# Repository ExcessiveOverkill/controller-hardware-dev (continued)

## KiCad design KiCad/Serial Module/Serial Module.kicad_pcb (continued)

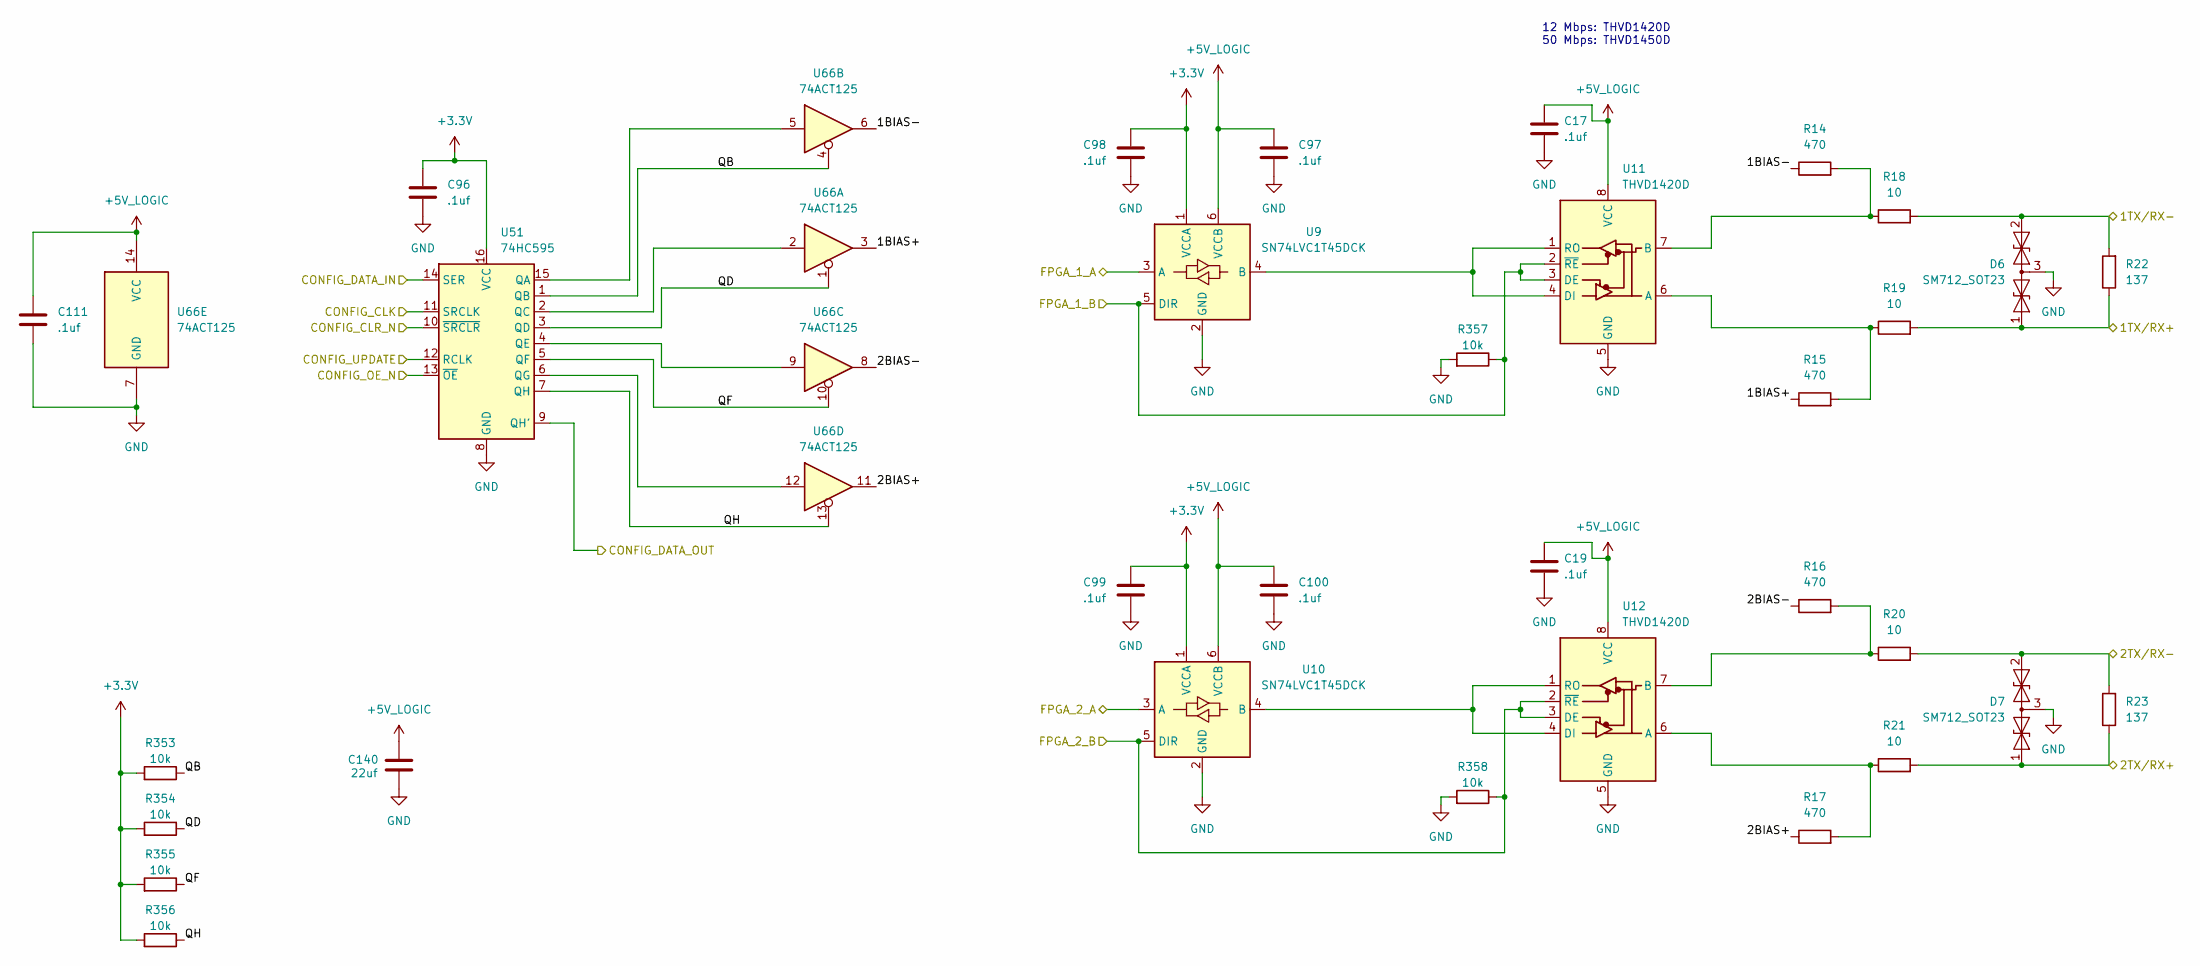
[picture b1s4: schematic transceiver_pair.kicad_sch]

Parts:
C17, C19, C96, C97, C98, C99, C100, C111: .1uf; C_0402_1005Metric; Part number CC0402KRX7R9BB104; LCSC# C131394
C140: 22uf; C_0805_2012Metric; Part number CC0805MKX5R8BB226; LCSC# C784585
D6, D7: SM712_SOT23; SOT-23; Part number SM712; LCSC# C502564
R14, R15, R16, R17: 470; R_0805_2012Metric; Part number 0603WAF4700T5E; LCSC# C23179
R18, R19, R20, R21: 10; R_0603_1608Metric; Part number 0603WAF100JT5E; LCSC# C22859
R22, R23: 137; R_0603_1608Metric; Part number 0603WAF1370T5E; LCSC# C22873
R353, R354, R355, R356, R357, R358: 10k; R_0402_1005Metric; Part number RC0402FR-0710KL; LCSC# C60490
U9, U10: SN74LVC1T45DCK; SOT-363_SC-70-6; Part number SN74LVC1T45DCKR; LCSC# C9382
U11, U12: THVD1420D; SOIC-8_3.9x4.9mm_P1.27mm; Part number THVD1420DR; LCSC# C3235215
U51: 74HC595; DHVQFN-16-1EP_2.5x3.5mm_P0.5mm_EP1x2mm; Part number 74HC595BQ,115; LCSC# C730243
U66: 74ACT125; TSSOP-14_4.4x5mm_P0.65mm; Part number SN74ACT125PWR; LCSC# C52940839

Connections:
+3.3V: C96.1, C98.1, C99.1, R353.2, R354.2, R355.2, R356.2, U9.1 (VCCA), U10.1 (VCCA), U51.16 (VCC); also elsewhere on the board
+5V_LOGIC: C17.1, C19.1, C97.1, C100.1, C111.1, C140.2, U9.6 (VCCB), U10.6 (VCCB), U11.8 (VCC), U12.8 (VCC), U66.14 (VCC); also elsewhere on the board
/MCU/CONFIG_CLK: U51.11 (SRCLK); also elsewhere on the board
/MCU/CONFIG_CLR_N: U51.10 (~SRCLR); also elsewhere on the board
/MCU/CONFIG_DATA: U51.14 (SER); also elsewhere on the board
/MCU/CONFIG_OE_N: U51.13 (~OE); also elsewhere on the board
/MCU/CONFIG_UPDATE: U51.12 (RCLK); also elsewhere on the board
/Transceivers/FPGA MUX/FPGA_PORT_1_PIN_0: U9.3 (A); also elsewhere on the board
/Transceivers/FPGA MUX/FPGA_PORT_1_PIN_1: R357.1, U9.5 (DIR), U11.2 (~RE), U11.3 (DE); also elsewhere on the board
/Transceivers/FPGA MUX/FPGA_PORT_1_PIN_2: U10.3 (A); also elsewhere on the board
/Transceivers/FPGA MUX/FPGA_PORT_1_PIN_3: R358.1, U10.5 (DIR), U12.2 (~RE), U12.3 (DE); also elsewhere on the board
/Transceivers/PORT_1_DATA_1+: D6.1 (A1), R19.2, R22.1; also elsewhere on the board
/Transceivers/PORT_1_DATA_1-: D6.2 (A2), R18.2, R22.2; also elsewhere on the board
/Transceivers/PORT_1_DATA_2+: D7.1 (A1), R21.2, R23.1; also elsewhere on the board
/Transceivers/PORT_1_DATA_2-: D7.2 (A2), R20.2, R23.2; also elsewhere on the board
/Transceivers/Transceiver pair/1BIAS+: R15.1, U66.3
/Transceivers/Transceiver pair/1BIAS-: R14.1, U66.6
/Transceivers/Transceiver pair/2BIAS+: R17.1, U66.11
/Transceivers/Transceiver pair/2BIAS-: R16.1, U66.8
/Transceivers/Transceiver pair/CONFIG_DATA_OUT: U51.9 (QH'); also elsewhere on the board
/Transceivers/Transceiver pair/QB: R353.1, U51.1 (QB), U66.4
/Transceivers/Transceiver pair/QD: R354.1, U51.3 (QD), U66.1
/Transceivers/Transceiver pair/QF: R355.1, U51.5 (QF), U66.10
/Transceivers/Transceiver pair/QH: R356.1, U51.7 (QH), U66.13
GND: C17.2, C19.2, C96.2, C97.2, C98.2, C99.2, C100.2, C111.2, C140.1, D6.3 (common), D7.3 (common), R357.2, R358.2, U9.2 (GND), U10.2 (GND), U11.5 (GND), U12.5 (GND), U51.8 (GND), U66.7 (GND); also elsewhere on the board
unnamed: U10.4 (B), U12.1 (RO), U12.4 (DI)
unnamed: R15.2, R19.1, U11.6 (A)
unnamed: R14.2, R18.1, U11.7 (B)
unnamed: U9.4 (B), U11.1 (RO), U11.4 (DI)
unnamed: R17.2, R21.1, U12.6 (A)
unnamed: R16.2, R20.1, U12.7 (B)
unnamed: U51.15 (QA), U66.5
unnamed: U51.2 (QC), U66.2
unnamed: U51.4 (QE), U66.9
unnamed: U51.6 (QG), U66.12

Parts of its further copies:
C25, C26, C31, C32, C79, C80, C81, C82, C83, C84, C85, C86, C87, C88, C103, C104, C105, C106, C107, C108, C109, C117, C118, C119, C120, C121, C122, C123, C124, C125, C126, C127, C128, C129, C130, C131, C145, C146, C147, C160, C161, C162, C163, C164, C165, C167, C168, C169, C170, C171, C172, C174, C175, C176, C177, C178: .1uf; C_0402_1005Metric; Part number CC0402KRX7R9BB104; LCSC# C131394
C141, C142, C143, C144, C159, C166, C173: 22uf; C_0805_2012Metric; Part number CC0805MKX5R8BB226; LCSC# C784585
D36, D37, D38, D39, D40, D41, D42, D43, D44, D45, D46, D47, D48, D49: SM712_SOT23; SOT-23; Part number SM712; LCSC# C502564
R64, R65, R66, R67, R74, R75, R76, R77, R84, R85, R86, R87, R94, R95, R96, R97, R104, R105, R106, R107, R114, R115, R116, R117, R124, R125, R126, R127: 470; R_0805_2012Metric; Part number 0603WAF4700T5E; LCSC# C23179
R68, R69, R70, R71, R78, R79, R80, R81, R88, R89, R90, R91, R98, R99, R100, R101, R108, R109, R110, R111, R118, R119, R120, R121, R128, R129, R130, R131: 10; R_0603_1608Metric; Part number 0603WAF100JT5E; LCSC# C22859
R72, R73, R82, R83, R92, R93, R102, R103, R112, R113, R122, R123, R132, R133: 137; R_0603_1608Metric; Part number 0603WAF1370T5E; LCSC# C22873
R359, R360, R361, R362, R363, R364, R365, R366, R367, R368, R369, R370, R371, R372, R373, R374, R375, R376, R377, R378, R379, R380, R381, R382, R383, R384, R405, R406, R407, R408, R409, R410, R411, R412, R413, R414, R415, R416, R417, R418, R419, R420: 10k; R_0402_1005Metric; Part number RC0402FR-0710KL; LCSC# C60490
U16, U17, U28, U29, U32, U33, U36, U37, U40, U41, U44, U45, U48, U49: SN74LVC1T45DCK; SOT-363_SC-70-6; Part number SN74LVC1T45DCKR; LCSC# C9382
U26, U27, U30, U31, U34, U35, U38, U39, U42, U43, U46, U47, U50, U61: THVD1420D; SOIC-8_3.9x4.9mm_P1.27mm; Part number THVD1420DR; LCSC# C3235215
U54, U55, U56, U57, U58, U59, U60: 74HC595; DHVQFN-16-1EP_2.5x3.5mm_P0.5mm_EP1x2mm; Part number 74HC595BQ,115; LCSC# C730243
U67, U68, U69, U70, U71, U72, U73: 74ACT125; TSSOP-14_4.4x5mm_P0.65mm; Part number SN74ACT125PWR; LCSC# C52940839

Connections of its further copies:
+3.3V: C103.1, C104.1, C105.1, C108.1, C109.1, C119.1, C123.1, C124.1, C125.1, C129.1, C130.1, C131.1, C160.1, C161.1, C162.1, C167.1, C168.1, C169.1, C174.1, C175.1, C176.1, R359.2, R360.2, R361.2, R362.2, R365.2, R366.2, R367.2, R368.2, R371.2, R372.2, R373.2, R374.2, R377.2, R378.2, R379.2, R380.2, R383.2, R384.2, R405.2, R406.2, R409.2, R410.2, R411.2, R412.2, R415.2, R416.2, R417.2, R418.2, U16.1 (VCCA), U17.1 (VCCA), U28.1 (VCCA), U29.1 (VCCA), U32.1 (VCCA), U33.1 (VCCA), U36.1 (VCCA), U37.1 (VCCA), U40.1 (VCCA), U41.1 (VCCA), U44.1 (VCCA), U45.1 (VCCA), U48.1 (VCCA), U49.1 (VCCA), U54.16 (VCC), U55.16 (VCC), U56.16 (VCC), U57.16 (VCC), U58.16 (VCC), U59.16 (VCC), U60.16 (VCC); also elsewhere on the board
+5V_LOGIC: C25.1, C26.1, C31.1, C32.1, C79.1, C80.1, C81.1, C82.1, C83.1, C84.1, C85.1, C86.1, C87.1, C88.1, C106.1, C107.1, C117.1, C118.1, C120.1, C121.1, C122.1, C126.1, C127.1, C128.1, C141.2, C142.2, C143.2, C144.2, C145.1, C146.1, C147.1, C159.2, C163.1, C164.1, C165.1, C166.2, C170.1, C171.1, C172.1, C173.2, C177.1, C178.1, U16.6 (VCCB), U17.6 (VCCB), U26.8 (VCC), U27.8 (VCC), U28.6 (VCCB), U29.6 (VCCB), U30.8 (VCC), U31.8 (VCC), U32.6 (VCCB), U33.6 (VCCB), U34.8 (VCC), U35.8 (VCC), U36.6 (VCCB), U37.6 (VCCB), U38.8 (VCC), U39.8 (VCC), U40.6 (VCCB), U41.6 (VCCB), U42.8 (VCC), U43.8 (VCC), U44.6 (VCCB), U45.6 (VCCB), U46.8 (VCC), U47.8 (VCC), U48.6 (VCCB), U49.6 (VCCB), U50.8 (VCC), U61.8 (VCC), U67.14 (VCC), U68.14 (VCC), U69.14 (VCC), U70.14 (VCC), U71.14 (VCC), U72.14 (VCC), U73.14 (VCC); also elsewhere on the board
/MCU/CONFIG_CLK: U54.11 (SRCLK), U55.11 (SRCLK), U56.11 (SRCLK), U57.11 (SRCLK), U58.11 (SRCLK), U59.11 (SRCLK), U60.11 (SRCLK); also elsewhere on the board
/MCU/CONFIG_CLR_N: U54.10 (~SRCLR), U55.10 (~SRCLR), U56.10 (~SRCLR), U57.10 (~SRCLR), U58.10 (~SRCLR), U59.10 (~SRCLR), U60.10 (~SRCLR); also elsewhere on the board
/MCU/CONFIG_OE_N: U54.13 (~OE), U55.13 (~OE), U56.13 (~OE), U57.13 (~OE), U58.13 (~OE), U59.13 (~OE), U60.13 (~OE); also elsewhere on the board
/MCU/CONFIG_UPDATE: U54.12 (RCLK), U55.12 (RCLK), U56.12 (RCLK), U57.12 (RCLK), U58.12 (RCLK), U59.12 (RCLK), U60.12 (RCLK); also elsewhere on the board
/Transceivers/FPGA MUX/FPGA_PORT_2_PIN_0: U16.3 (A); also elsewhere on the board
/Transceivers/FPGA MUX/FPGA_PORT_2_PIN_1: R363.1, U16.5 (DIR), U26.2 (~RE), U26.3 (DE); also elsewhere on the board
/Transceivers/FPGA MUX/FPGA_PORT_2_PIN_2: U17.3 (A); also elsewhere on the board
/Transceivers/FPGA MUX/FPGA_PORT_2_PIN_3: R364.1, U17.5 (DIR), U27.2 (~RE), U27.3 (DE); also elsewhere on the board
/Transceivers/FPGA MUX/FPGA_PORT_3_PIN_0: U28.3 (A); also elsewhere on the board
/Transceivers/FPGA MUX/FPGA_PORT_3_PIN_1: R369.1, U28.5 (DIR), U30.2 (~RE), U30.3 (DE); also elsewhere on the board
/Transceivers/FPGA MUX/FPGA_PORT_3_PIN_2: U29.3 (A); also elsewhere on the board
/Transceivers/FPGA MUX/FPGA_PORT_3_PIN_3: R370.1, U29.5 (DIR), U31.2 (~RE), U31.3 (DE); also elsewhere on the board
/Transceivers/FPGA MUX/FPGA_PORT_4_PIN_0: U32.3 (A); also elsewhere on the board
/Transceivers/FPGA MUX/FPGA_PORT_4_PIN_1: R375.1, U32.5 (DIR), U34.2 (~RE), U34.3 (DE); also elsewhere on the board
/Transceivers/FPGA MUX/FPGA_PORT_4_PIN_2: U33.3 (A); also elsewhere on the board
/Transceivers/FPGA MUX/FPGA_PORT_4_PIN_3: R376.1, U33.5 (DIR), U35.2 (~RE), U35.3 (DE); also elsewhere on the board
/Transceivers/FPGA MUX/FPGA_PORT_5_PIN_0: U36.3 (A); also elsewhere on the board
/Transceivers/FPGA MUX/FPGA_PORT_5_PIN_1: R381.1, U36.5 (DIR), U38.2 (~RE), U38.3 (DE); also elsewhere on the board
/Transceivers/FPGA MUX/FPGA_PORT_5_PIN_2: U37.3 (A); also elsewhere on the board
/Transceivers/FPGA MUX/FPGA_PORT_5_PIN_3: R382.1, U37.5 (DIR), U39.2 (~RE), U39.3 (DE); also elsewhere on the board
/Transceivers/FPGA MUX/FPGA_PORT_6_PIN_0: U40.3 (A); also elsewhere on the board
/Transceivers/FPGA MUX/FPGA_PORT_6_PIN_1: R407.1, U40.5 (DIR), U42.2 (~RE), U42.3 (DE); also elsewhere on the board
/Transceivers/FPGA MUX/FPGA_PORT_6_PIN_2: U41.3 (A); also elsewhere on the board
/Transceivers/FPGA MUX/FPGA_PORT_6_PIN_3: R408.1, U41.5 (DIR), U43.2 (~RE), U43.3 (DE); also elsewhere on the board
/Transceivers/FPGA MUX/FPGA_PORT_7_PIN_0: U44.3 (A); also elsewhere on the board
/Transceivers/FPGA MUX/FPGA_PORT_7_PIN_1: R413.1, U44.5 (DIR), U46.2 (~RE), U46.3 (DE); also elsewhere on the board
/Transceivers/FPGA MUX/FPGA_PORT_7_PIN_2: U45.3 (A); also elsewhere on the board
/Transceivers/FPGA MUX/FPGA_PORT_7_PIN_3: R414.1, U45.5 (DIR), U47.2 (~RE), U47.3 (DE); also elsewhere on the board
/Transceivers/FPGA MUX/FPGA_PORT_8_PIN_0: U48.3 (A); also elsewhere on the board
/Transceivers/FPGA MUX/FPGA_PORT_8_PIN_1: R419.1, U48.5 (DIR), U50.2 (~RE), U50.3 (DE); also elsewhere on the board
/Transceivers/FPGA MUX/FPGA_PORT_8_PIN_2: U49.3 (A); also elsewhere on the board
/Transceivers/FPGA MUX/FPGA_PORT_8_PIN_3: R420.1, U49.5 (DIR), U61.2 (~RE), U61.3 (DE); also elsewhere on the board
/Transceivers/PORT_2_DATA_1+: D36.1 (A1), R69.2, R72.1; also elsewhere on the board
/Transceivers/PORT_2_DATA_1-: D36.2 (A2), R68.2, R72.2; also elsewhere on the board
/Transceivers/PORT_2_DATA_2+: D37.1 (A1), R71.2, R73.1; also elsewhere on the board
/Transceivers/PORT_2_DATA_2-: D37.2 (A2), R70.2, R73.2; also elsewhere on the board
/Transceivers/PORT_3_DATA_1+: D38.1 (A1), R79.2, R82.1; also elsewhere on the board
/Transceivers/PORT_3_DATA_1-: D38.2 (A2), R78.2, R82.2; also elsewhere on the board
/Transceivers/PORT_3_DATA_2+: D39.1 (A1), R81.2, R83.1; also elsewhere on the board
/Transceivers/PORT_3_DATA_2-: D39.2 (A2), R80.2, R83.2; also elsewhere on the board
/Transceivers/PORT_4_DATA_1+: D40.1 (A1), R89.2, R92.1; also elsewhere on the board
/Transceivers/PORT_4_DATA_1-: D40.2 (A2), R88.2, R92.2; also elsewhere on the board
/Transceivers/PORT_4_DATA_2+: D41.1 (A1), R91.2, R93.1; also elsewhere on the board
/Transceivers/PORT_4_DATA_2-: D41.2 (A2), R90.2, R93.2; also elsewhere on the board
/Transceivers/PORT_5_DATA_1+: D42.1 (A1), R99.2, R102.1; also elsewhere on the board
/Transceivers/PORT_5_DATA_1-: D42.2 (A2), R98.2, R102.2; also elsewhere on the board
/Transceivers/PORT_5_DATA_2+: D43.1 (A1), R101.2, R103.1; also elsewhere on the board
/Transceivers/PORT_5_DATA_2-: D43.2 (A2), R100.2, R103.2; also elsewhere on the board
/Transceivers/PORT_6_DATA_1+: D44.1 (A1), R109.2, R112.1; also elsewhere on the board
/Transceivers/PORT_6_DATA_1-: D44.2 (A2), R108.2, R112.2; also elsewhere on the board
/Transceivers/PORT_6_DATA_2+: D45.1 (A1), R111.2, R113.1; also elsewhere on the board
/Transceivers/PORT_6_DATA_2-: D45.2 (A2), R110.2, R113.2; also elsewhere on the board
/Transceivers/PORT_7_DATA_1+: D46.1 (A1), R119.2, R122.1; also elsewhere on the board
/Transceivers/PORT_7_DATA_1-: D46.2 (A2), R118.2, R122.2; also elsewhere on the board
/Transceivers/PORT_7_DATA_2+: D47.1 (A1), R121.2, R123.1; also elsewhere on the board
/Transceivers/PORT_7_DATA_2-: D47.2 (A2), R120.2, R123.2; also elsewhere on the board
/Transceivers/PORT_8_DATA_1+: D48.1 (A1), R129.2, R132.1; also elsewhere on the board
/Transceivers/PORT_8_DATA_1-: D48.2 (A2), R128.2, R132.2; also elsewhere on the board
/Transceivers/PORT_8_DATA_2+: D49.1 (A1), R131.2, R133.1; also elsewhere on the board
/Transceivers/PORT_8_DATA_2-: D49.2 (A2), R130.2, R133.2; also elsewhere on the board
/Transceivers/Port Power/CONFIG_DATA_IN: U60.9 (QH'); also elsewhere on the board
/Transceivers/Transceiver pair1/1BIAS+: R65.1, U67.3
/Transceivers/Transceiver pair1/1BIAS-: R64.1, U67.6
/Transceivers/Transceiver pair1/2BIAS+: R67.1, U67.11
/Transceivers/Transceiver pair1/2BIAS-: R66.1, U67.8
/Transceivers/Transceiver pair1/CONFIG_DATA_OUT: U54.9 (QH'), U55.14 (SER)
/Transceivers/Transceiver pair1/QB: R359.1, U54.1 (QB), U67.4
/Transceivers/Transceiver pair1/QD: R360.1, U54.3 (QD), U67.1
/Transceivers/Transceiver pair1/QF: R361.1, U54.5 (QF), U67.10
/Transceivers/Transceiver pair1/QH: R362.1, U54.7 (QH), U67.13
/Transceivers/Transceiver pair2/1BIAS+: R75.1, U68.3
/Transceivers/Transceiver pair2/1BIAS-: R74.1, U68.6
/Transceivers/Transceiver pair2/2BIAS+: R77.1, U68.11
/Transceivers/Transceiver pair2/2BIAS-: R76.1, U68.8
/Transceivers/Transceiver pair2/CONFIG_DATA_OUT: U55.9 (QH'), U56.14 (SER)
/Transceivers/Transceiver pair2/QB: R365.1, U55.1 (QB), U68.4
/Transceivers/Transceiver pair2/QD: R366.1, U55.3 (QD), U68.1
/Transceivers/Transceiver pair2/QF: R367.1, U55.5 (QF), U68.10
/Transceivers/Transceiver pair2/QH: R368.1, U55.7 (QH), U68.13
/Transceivers/Transceiver pair3/1BIAS+: R85.1, U69.3
/Transceivers/Transceiver pair3/1BIAS-: R84.1, U69.6
/Transceivers/Transceiver pair3/2BIAS+: R87.1, U69.11
/Transceivers/Transceiver pair3/2BIAS-: R86.1, U69.8
/Transceivers/Transceiver pair3/CONFIG_DATA_OUT: U56.9 (QH'), U57.14 (SER)
/Transceivers/Transceiver pair3/QB: R371.1, U56.1 (QB), U69.4
/Transceivers/Transceiver pair3/QD: R372.1, U56.3 (QD), U69.1
/Transceivers/Transceiver pair3/QF: R373.1, U56.5 (QF), U69.10
/Transceivers/Transceiver pair3/QH: R374.1, U56.7 (QH), U69.13
/Transceivers/Transceiver pair4/1BIAS+: R95.1, U70.3
/Transceivers/Transceiver pair4/1BIAS-: R94.1, U70.6
/Transceivers/Transceiver pair4/2BIAS+: R97.1, U70.11
/Transceivers/Transceiver pair4/2BIAS-: R96.1, U70.8
/Transceivers/Transceiver pair4/CONFIG_DATA_OUT: U57.9 (QH'), U58.14 (SER)
/Transceivers/Transceiver pair4/QB: R377.1, U57.1 (QB), U70.4
/Transceivers/Transceiver pair4/QD: R378.1, U57.3 (QD), U70.1
/Transceivers/Transceiver pair4/QF: R379.1, U57.5 (QF), U70.10
/Transceivers/Transceiver pair4/QH: R380.1, U57.7 (QH), U70.13
/Transceivers/Transceiver pair5/1BIAS+: R105.1, U71.3
/Transceivers/Transceiver pair5/1BIAS-: R104.1, U71.6
/Transceivers/Transceiver pair5/2BIAS+: R107.1, U71.11
/Transceivers/Transceiver pair5/2BIAS-: R106.1, U71.8
/Transceivers/Transceiver pair5/CONFIG_DATA_OUT: U58.9 (QH'), U59.14 (SER)
/Transceivers/Transceiver pair5/QB: R383.1, U58.1 (QB), U71.4
/Transceivers/Transceiver pair5/QD: R384.1, U58.3 (QD), U71.1
/Transceivers/Transceiver pair5/QF: R405.1, U58.5 (QF), U71.10
/Transceivers/Transceiver pair5/QH: R406.1, U58.7 (QH), U71.13
/Transceivers/Transceiver pair6/1BIAS+: R115.1, U72.3
/Transceivers/Transceiver pair6/1BIAS-: R114.1, U72.6
/Transceivers/Transceiver pair6/2BIAS+: R117.1, U72.11
/Transceivers/Transceiver pair6/2BIAS-: R116.1, U72.8
/Transceivers/Transceiver pair6/CONFIG_DATA_OUT: U59.9 (QH'), U60.14 (SER)
/Transceivers/Transceiver pair6/QB: R409.1, U59.1 (QB), U72.4
/Transceivers/Transceiver pair6/QD: R410.1, U59.3 (QD), U72.1
/Transceivers/Transceiver pair6/QF: R411.1, U59.5 (QF), U72.10
/Transceivers/Transceiver pair6/QH: R412.1, U59.7 (QH), U72.13
/Transceivers/Transceiver pair7/1BIAS+: R125.1, U73.3
/Transceivers/Transceiver pair7/1BIAS-: R124.1, U73.6
/Transceivers/Transceiver pair7/2BIAS+: R127.1, U73.11
/Transceivers/Transceiver pair7/2BIAS-: R126.1, U73.8
/Transceivers/Transceiver pair7/QB: R415.1, U60.1 (QB), U73.4
/Transceivers/Transceiver pair7/QD: R416.1, U60.3 (QD), U73.1
/Transceivers/Transceiver pair7/QF: R417.1, U60.5 (QF), U73.10
/Transceivers/Transceiver pair7/QH: R418.1, U60.7 (QH), U73.13
/Transceivers/Transceiver pair/CONFIG_DATA_OUT: U54.14 (SER); also elsewhere on the board
GND: C25.2, C26.2, C31.2, C32.2, C79.2, C80.2, C81.2, C82.2, C83.2, C84.2, C85.2, C86.2, C87.2, C88.2, C103.2, C104.2, C105.2, C106.2, C107.2, C108.2, C109.2, C117.2, C118.2, C119.2, C120.2, C121.2, C122.2, C123.2, C124.2, C125.2, C126.2, C127.2, C128.2, C129.2, C130.2, C131.2, C141.1, C142.1, C143.1, C144.1, C145.2, C146.2, C147.2, C159.1, C160.2, C161.2, C162.2, C163.2, C164.2, C165.2, C166.1, C167.2, C168.2, C169.2, C170.2, C171.2, C172.2, C173.1, C174.2, C175.2, C176.2, C177.2, C178.2, D36.3 (common), D37.3 (common), D38.3 (common), D39.3 (common), D40.3 (common), D41.3 (common), D42.3 (common), D43.3 (common), D44.3 (common), D45.3 (common), D46.3 (common), D47.3 (common), D48.3 (common), D49.3 (common), R363.2, R364.2, R369.2, R370.2, R375.2, R376.2, R381.2, R382.2, R407.2, R408.2, R413.2, R414.2, R419.2, R420.2, U16.2 (GND), U17.2 (GND), U26.5 (GND), U27.5 (GND), U28.2 (GND), U29.2 (GND), U30.5 (GND), U31.5 (GND), U32.2 (GND), U33.2 (GND), U34.5 (GND), U35.5 (GND), U36.2 (GND), U37.2 (GND), U38.5 (GND), U39.5 (GND), U40.2 (GND), U41.2 (GND), U42.5 (GND), U43.5 (GND), U44.2 (GND), U45.2 (GND), U46.5 (GND), U47.5 (GND), U48.2 (GND), U49.2 (GND), U50.5 (GND), U54.8 (GND), U55.8 (GND), U56.8 (GND), U57.8 (GND), U58.8 (GND), U59.8 (GND), U60.8 (GND), U61.5 (GND), U67.7 (GND), U68.7 (GND), U69.7 (GND), U70.7 (GND), U71.7 (GND), U72.7 (GND), U73.7 (GND); also elsewhere on the board
unnamed: U16.4 (B), U26.1 (RO), U26.4 (DI)
unnamed: U17.4 (B), U27.1 (RO), U27.4 (DI)
unnamed: R65.2, R69.1, U26.6 (A)
unnamed: R64.2, R68.1, U26.7 (B)
unnamed: R67.2, R71.1, U27.6 (A)
unnamed: R66.2, R70.1, U27.7 (B)
unnamed: U28.4 (B), U30.1 (RO), U30.4 (DI)
unnamed: U29.4 (B), U31.1 (RO), U31.4 (DI)
unnamed: R75.2, R79.1, U30.6 (A)
unnamed: R74.2, R78.1, U30.7 (B)
unnamed: R77.2, R81.1, U31.6 (A)
unnamed: R76.2, R80.1, U31.7 (B)
unnamed: U32.4 (B), U34.1 (RO), U34.4 (DI)
unnamed: U33.4 (B), U35.1 (RO), U35.4 (DI)
unnamed: R85.2, R89.1, U34.6 (A)
unnamed: R84.2, R88.1, U34.7 (B)
unnamed: R87.2, R91.1, U35.6 (A)
unnamed: R86.2, R90.1, U35.7 (B)
unnamed: U36.4 (B), U38.1 (RO), U38.4 (DI)
unnamed: U37.4 (B), U39.1 (RO), U39.4 (DI)
unnamed: R95.2, R99.1, U38.6 (A)
unnamed: R94.2, R98.1, U38.7 (B)
unnamed: R97.2, R101.1, U39.6 (A)
unnamed: R96.2, R100.1, U39.7 (B)
unnamed: U40.4 (B), U42.1 (RO), U42.4 (DI)
unnamed: U41.4 (B), U43.1 (RO), U43.4 (DI)
unnamed: R105.2, R109.1, U42.6 (A)
unnamed: R104.2, R108.1, U42.7 (B)
unnamed: R107.2, R111.1, U43.6 (A)
unnamed: R106.2, R110.1, U43.7 (B)
unnamed: U44.4 (B), U46.1 (RO), U46.4 (DI)
unnamed: U45.4 (B), U47.1 (RO), U47.4 (DI)
unnamed: R115.2, R119.1, U46.6 (A)
unnamed: R114.2, R118.1, U46.7 (B)
unnamed: R117.2, R121.1, U47.6 (A)
unnamed: R116.2, R120.1, U47.7 (B)
unnamed: U48.4 (B), U50.1 (RO), U50.4 (DI)
unnamed: U49.4 (B), U61.1 (RO), U61.4 (DI)
unnamed: R125.2, R129.1, U50.6 (A)
unnamed: R124.2, R128.1, U50.7 (B)
unnamed: U54.15 (QA), U67.5
unnamed: U54.2 (QC), U67.2
unnamed: U54.4 (QE), U67.9
unnamed: U54.6 (QG), U67.12
unnamed: U55.15 (QA), U68.5
unnamed: U55.2 (QC), U68.2
unnamed: U55.4 (QE), U68.9
unnamed: U55.6 (QG), U68.12
unnamed: U56.15 (QA), U69.5
unnamed: U56.2 (QC), U69.2
unnamed: U56.4 (QE), U69.9
unnamed: U56.6 (QG), U69.12
unnamed: U57.15 (QA), U70.5
unnamed: U57.2 (QC), U70.2
unnamed: U57.4 (QE), U70.9
unnamed: U57.6 (QG), U70.12
unnamed: U58.15 (QA), U71.5
unnamed: U58.2 (QC), U71.2
unnamed: U58.4 (QE), U71.9
unnamed: U58.6 (QG), U71.12
unnamed: U59.15 (QA), U72.5
unnamed: U59.2 (QC), U72.2
unnamed: U59.4 (QE), U72.9
unnamed: U59.6 (QG), U72.12
unnamed: U60.15 (QA), U73.5
unnamed: U60.2 (QC), U73.2
unnamed: U60.4 (QE), U73.9
unnamed: U60.6 (QG), U73.12
unnamed: R127.2, R131.1, U61.6 (A)
unnamed: R126.2, R130.1, U61.7 (B)

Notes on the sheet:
12 Mbps: THVD1420D 50 Mbps: THVD1450D

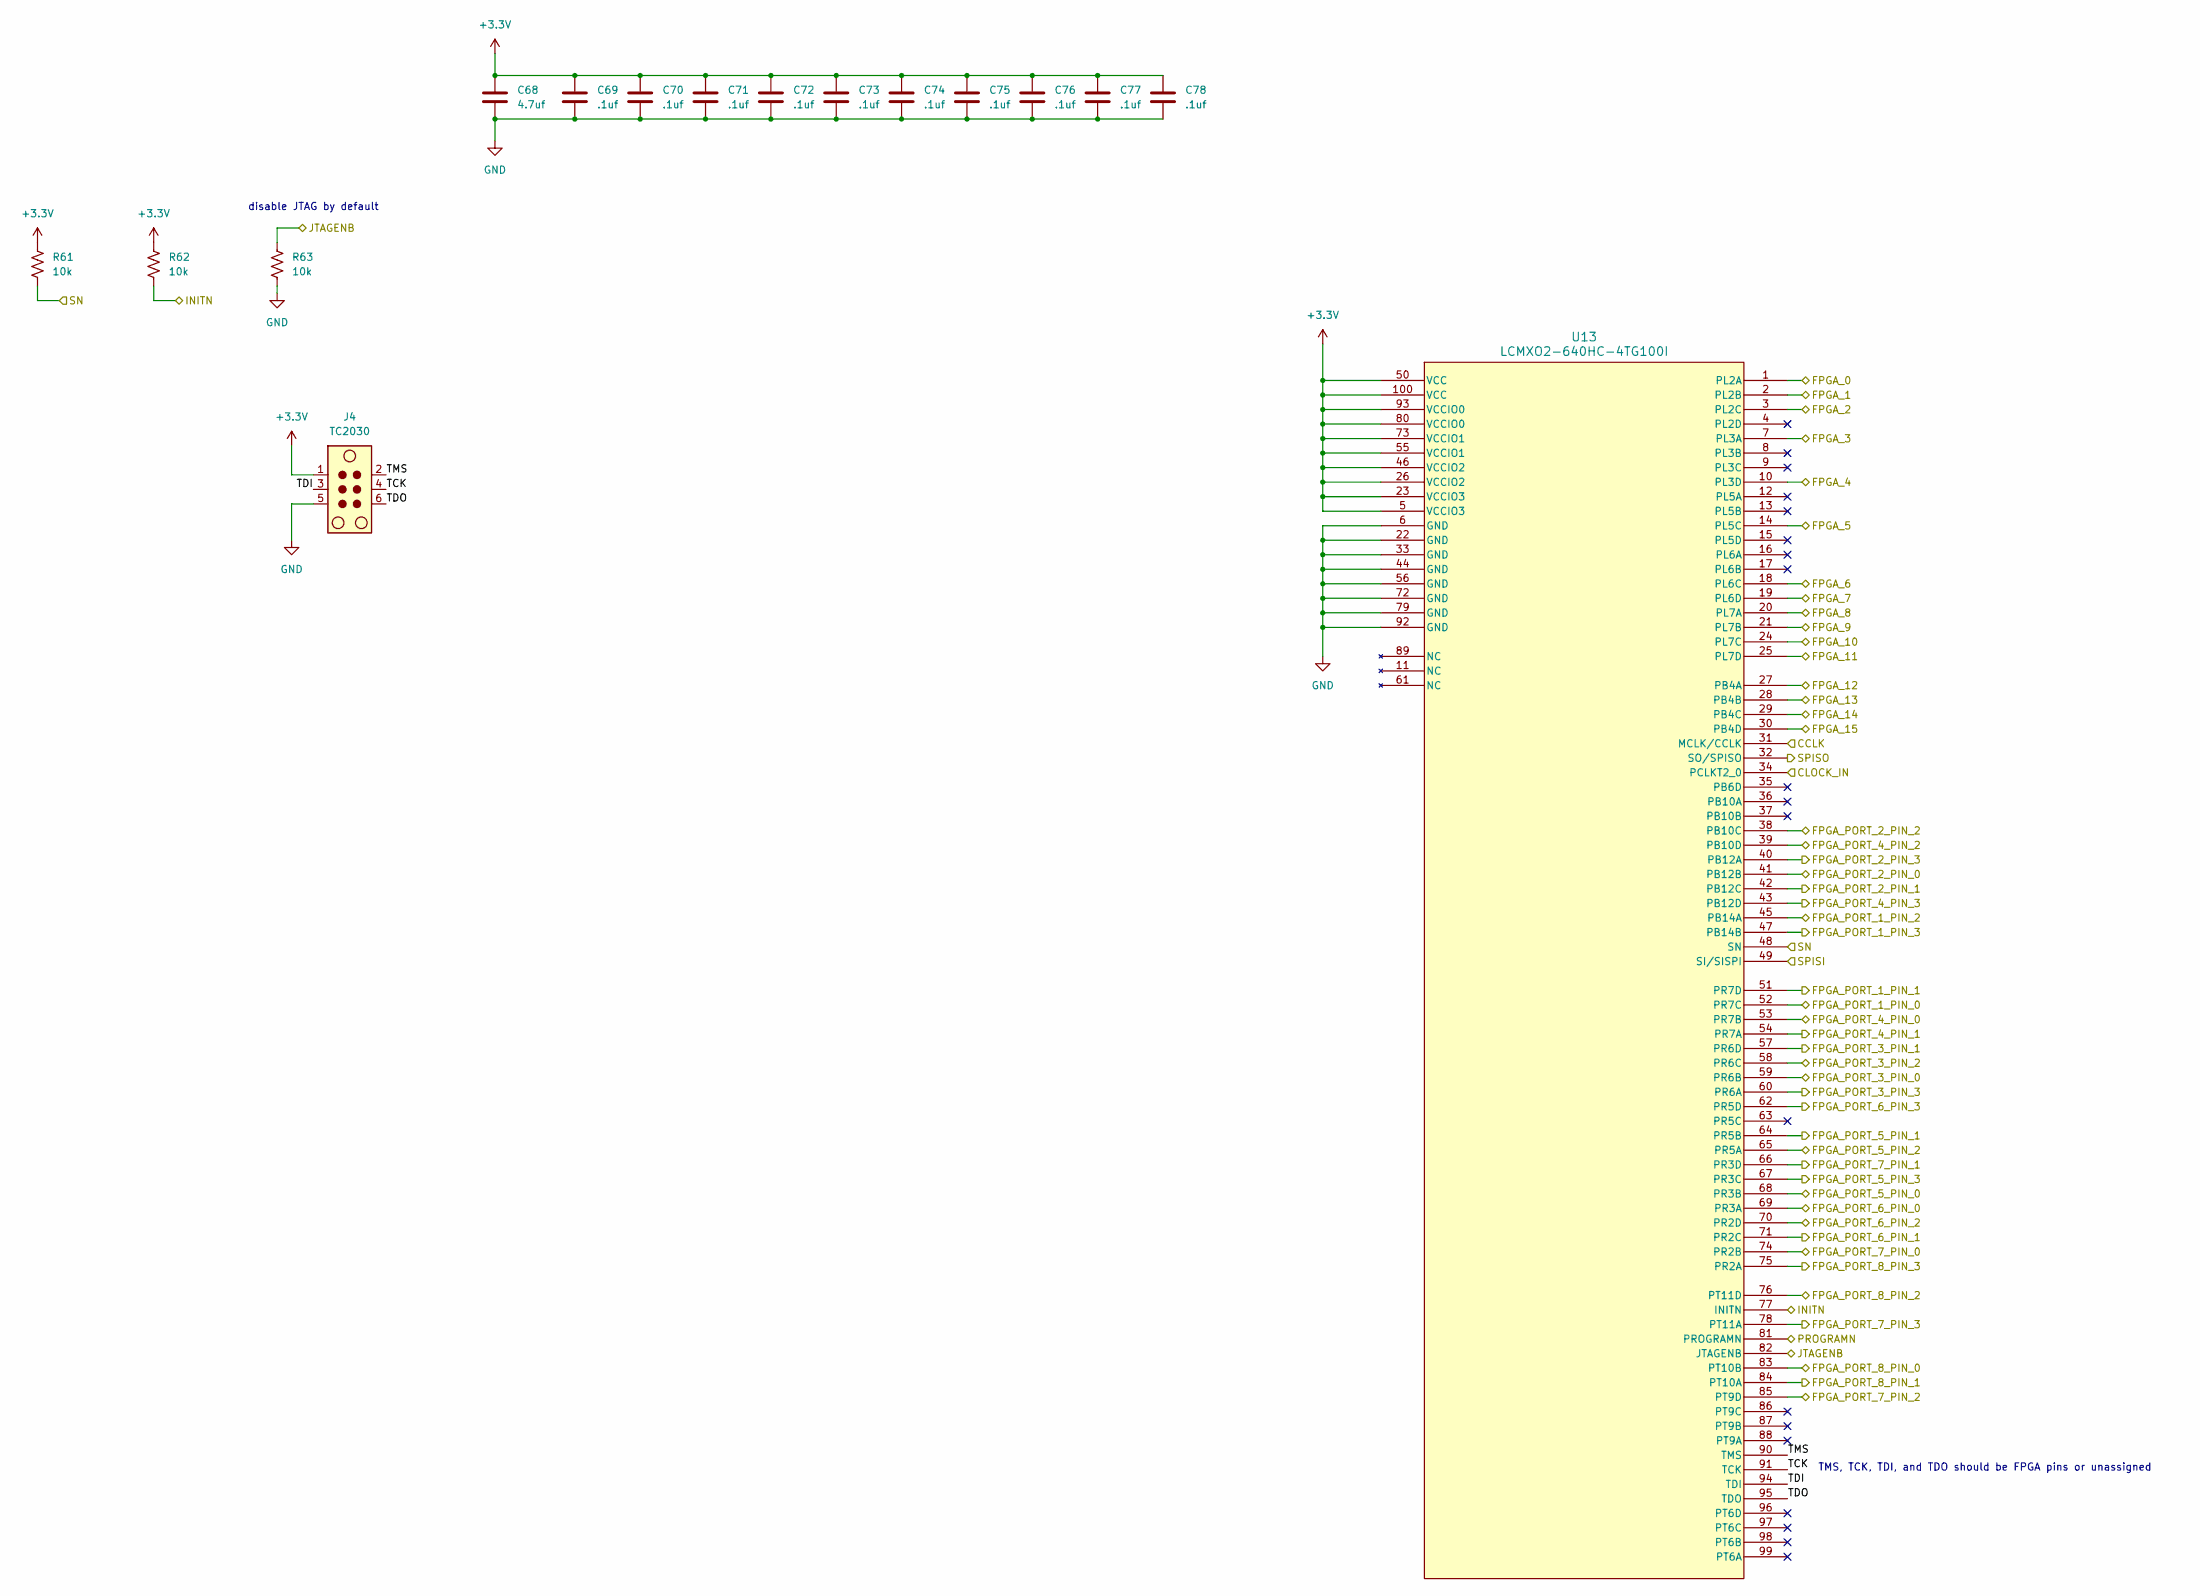
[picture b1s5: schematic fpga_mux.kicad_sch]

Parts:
C68: 4.7uf; C_0603_1608Metric; Part number CC0603KRX5R7BB475; LCSC# C277476
C69, C70, C71, C72, C73, C74, C75, C76, C77, C78: .1uf; C_0402_1005Metric; Part number CC0402KRX7R9BB104; LCSC# C131394
J4: TC2030; Tag-Connect_TC2030-IDC-FP_2x03_P1.27mm_Vertical
R61, R62, R63: 10k; R_0402_1005Metric; Part number RC0402FR-0710KL; LCSC# C60490
U13: LCMXO2-640HC-4TG100I; TQFP100_LAT; Part number LCMXO2-640HC-4TG100I; LCSC# C5680157

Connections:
+3.3V: C68.1, C69.1, C70.1, C71.1, C72.1, C73.1, C74.1, C75.1, C76.1, C77.1, C78.1, J4.1, R61.2, R62.2, U13.5 (VCCIO3), U13.23 (VCCIO3), U13.26 (VCCIO2), U13.46 (VCCIO2), U13.50 (VCC), U13.55 (VCCIO1), U13.73 (VCCIO1), U13.80 (VCCIO0), U13.93 (VCCIO0), U13.100 (VCC); also elsewhere on the board
/FPGA Connector/IN_0: U13.99 (PT6A); also elsewhere on the board
/FPGA Connector/IN_1: U13.98 (PT6B); also elsewhere on the board
/FPGA Connector/IN_2: U13.97 (PT6C); also elsewhere on the board
/FPGA Connector/IN_3: U13.96 (PT6D); also elsewhere on the board
/FPGA Connector/IN_4: U13.88 (PT9A); also elsewhere on the board
/FPGA Connector/IN_5: U13.87 (PT9B); also elsewhere on the board
/FPGA Connector/IN_6: U13.86 (PT9C); also elsewhere on the board
/FPGA Connector/IN_7: U13.85 (PT9D); also elsewhere on the board
/FPGA Connector/IN_8: U13.84 (PT10A); also elsewhere on the board
/FPGA Connector/IN_9: U13.83 (PT10B); also elsewhere on the board
/FPGA Connector/IN_10: U13.78 (PT11A); also elsewhere on the board
/FPGA Connector/IN_11: U13.76 (PT11D); also elsewhere on the board
/FPGA Connector/IN_12: U13.75 (PR2A); also elsewhere on the board
/FPGA Connector/IN_13: U13.74 (PR2B); also elsewhere on the board
/FPGA Connector/IN_14: U13.71 (PR2C); also elsewhere on the board
/FPGA Connector/IN_15: U13.70 (PR2D); also elsewhere on the board
/MCU/CCLK: U13.31 (MCLK/CCLK); also elsewhere on the board
/MCU/FPGA_CLOCK: U13.34 (PCLKT2_0); also elsewhere on the board
/MCU/INITN: R62.1, U13.77 (INITN); also elsewhere on the board
/MCU/JTAGENB: R63.2, U13.82 (JTAGENB); also elsewhere on the board
/MCU/PROGRAMN: U13.81 (PROGRAMN); also elsewhere on the board
/MCU/SN: R61.1, U13.48 (SN); also elsewhere on the board
/MCU/SPISI: U13.49 (SI/SISPI); also elsewhere on the board
/MCU/SPISO: U13.32 (SO/SPISO); also elsewhere on the board
/Transceivers/FPGA MUX/FPGA_PORT_1_PIN_0: U13.14 (PL5C); also elsewhere on the board
/Transceivers/FPGA MUX/FPGA_PORT_1_PIN_1: U13.15 (PL5D); also elsewhere on the board
/Transceivers/FPGA MUX/FPGA_PORT_1_PIN_2: U13.12 (PL5A); also elsewhere on the board
/Transceivers/FPGA MUX/FPGA_PORT_1_PIN_3: U13.13 (PL5B); also elsewhere on the board
/Transceivers/FPGA MUX/FPGA_PORT_2_PIN_0: U13.18 (PL6C); also elsewhere on the board
/Transceivers/FPGA MUX/FPGA_PORT_2_PIN_1: U13.19 (PL6D); also elsewhere on the board
/Transceivers/FPGA MUX/FPGA_PORT_2_PIN_2: U13.16 (PL6A); also elsewhere on the board
/Transceivers/FPGA MUX/FPGA_PORT_2_PIN_3: U13.17 (PL6B); also elsewhere on the board
/Transceivers/FPGA MUX/FPGA_PORT_3_PIN_0: U13.24 (PL7C); also elsewhere on the board
/Transceivers/FPGA MUX/FPGA_PORT_3_PIN_1: U13.25 (PL7D); also elsewhere on the board
/Transceivers/FPGA MUX/FPGA_PORT_3_PIN_2: U13.20 (PL7A); also elsewhere on the board
/Transceivers/FPGA MUX/FPGA_PORT_3_PIN_3: U13.21 (PL7B); also elsewhere on the board
/Transceivers/FPGA MUX/FPGA_PORT_4_PIN_0: U13.30 (PB4D); also elsewhere on the board
/Transceivers/FPGA MUX/FPGA_PORT_4_PIN_1: U13.35 (PB6D); also elsewhere on the board
/Transceivers/FPGA MUX/FPGA_PORT_4_PIN_2: U13.28 (PB4B); also elsewhere on the board
/Transceivers/FPGA MUX/FPGA_PORT_4_PIN_3: U13.29 (PB4C); also elsewhere on the board
/Transceivers/FPGA MUX/FPGA_PORT_5_PIN_0: U13.38 (PB10C); also elsewhere on the board
/Transceivers/FPGA MUX/FPGA_PORT_5_PIN_1: U13.39 (PB10D); also elsewhere on the board
/Transceivers/FPGA MUX/FPGA_PORT_5_PIN_2: U13.36 (PB10A); also elsewhere on the board
/Transceivers/FPGA MUX/FPGA_PORT_5_PIN_3: U13.37 (PB10B); also elsewhere on the board
/Transceivers/FPGA MUX/FPGA_PORT_6_PIN_0: U13.53 (PR7B); also elsewhere on the board
/Transceivers/FPGA MUX/FPGA_PORT_6_PIN_1: U13.54 (PR7A); also elsewhere on the board
/Transceivers/FPGA MUX/FPGA_PORT_6_PIN_2: U13.51 (PR7D); also elsewhere on the board
/Transceivers/FPGA MUX/FPGA_PORT_6_PIN_3: U13.52 (PR7C); also elsewhere on the board
/Transceivers/FPGA MUX/FPGA_PORT_7_PIN_0: U13.59 (PR6B); also elsewhere on the board
/Transceivers/FPGA MUX/FPGA_PORT_7_PIN_1: U13.60 (PR6A); also elsewhere on the board
/Transceivers/FPGA MUX/FPGA_PORT_7_PIN_2: U13.57 (PR6D); also elsewhere on the board
/Transceivers/FPGA MUX/FPGA_PORT_7_PIN_3: U13.58 (PR6C); also elsewhere on the board
/Transceivers/FPGA MUX/FPGA_PORT_8_PIN_0: U13.64 (PR5B); also elsewhere on the board
/Transceivers/FPGA MUX/FPGA_PORT_8_PIN_1: U13.65 (PR5A); also elsewhere on the board
/Transceivers/FPGA MUX/FPGA_PORT_8_PIN_2: U13.62 (PR5D); also elsewhere on the board
/Transceivers/FPGA MUX/FPGA_PORT_8_PIN_3: U13.63 (PR5C); also elsewhere on the board
/Transceivers/FPGA MUX/TCK: J4.4, U13.91 (TCK)
/Transceivers/FPGA MUX/TDI: J4.3, U13.94 (TDI)
/Transceivers/FPGA MUX/TDO: J4.6, U13.95 (TDO)
/Transceivers/FPGA MUX/TMS: J4.2, U13.90 (TMS)
GND: C68.2, C69.2, C70.2, C71.2, C72.2, C73.2, C74.2, C75.2, C76.2, C77.2, C78.2, J4.5, R63.1, U13.6 (GND), U13.22 (GND), U13.33 (GND), U13.44 (GND), U13.56 (GND), U13.72 (GND), U13.79 (GND), U13.92 (GND); also elsewhere on the board

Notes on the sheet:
TMS, TCK, TDI, and TDO should be FPGA pins or unassigned
disable JTAG by default
